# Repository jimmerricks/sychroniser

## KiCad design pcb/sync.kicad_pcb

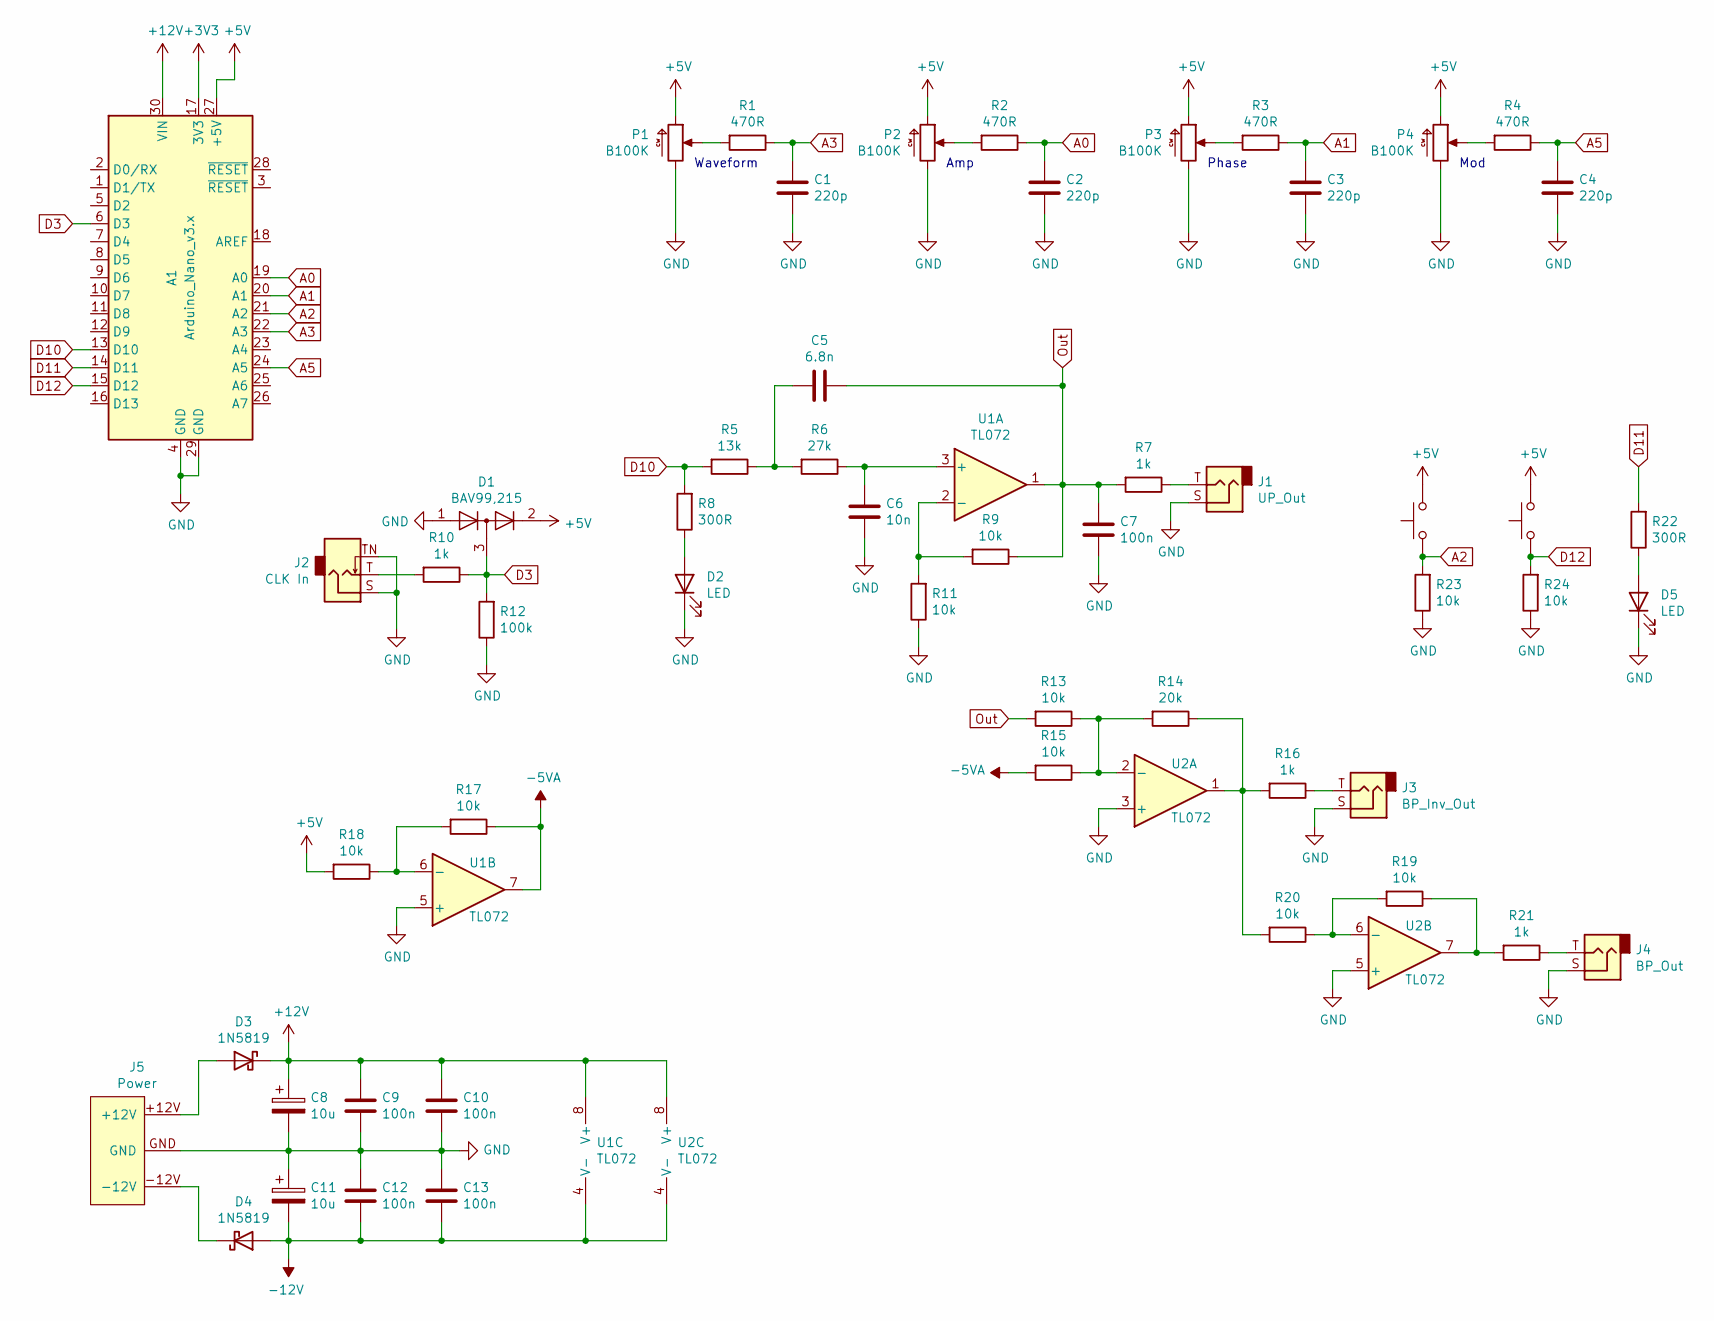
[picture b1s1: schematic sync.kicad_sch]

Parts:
A1: Arduino_Nano_v3.x; Arduino_Nano
C1, C2, C3, C4: 220p; C_0402_1005Metric; LCSC C1530
C5: 6.8n; C_0402_1005Metric; LCSC C1542
C6: 10n; C_0402_1005Metric; LCSC C15195
C7, C9, C10, C12, C13: 100n; C_0402_1005Metric; LCSC C1525
C8, C11: 10u; CP_EIA-3216-18_Kemet-A; LCSC C7171
D1: BAV99,215; SOT-23; LCSC C2500
D2, D5: LED; LED_D3.0mm
D3, D4: 1N5819; D_SOD-323; LCSC C191023
J1: UP_Out; Jack_3.5mm_QingPu_WQP-PJ301M-12
J2: CLK In; Jack_3.5mm_QingPu_WQP-PJ301M-12
J3: BP_Inv_Out; Jack_3.5mm_QingPu_WQP-PJ301M-12
J4: BP_Out; Jack_3.5mm_QingPu_WQP-PJ301M-12
J5: Power; Power_2x5_Vertical
P1, P3, P4: B100K; Potentiometer_AlpsAlpine_RK09L1140_wo_Fix
P2: B100K; Potentiometer_AlpsAlpine_RK09L1140
R1, R2, R3, R4: 470R; R_0402_1005Metric; LCSC C25117
R5: 13k; R_0603_1608Metric; LCSC C22797
R6: 27k; R_0402_1005Metric; LCSC C25771
R7, R10, R16, R21: 1k; R_0402_1005Metric; LCSC C11702
R8, R22: 300R; R_0402_1005Metric; LCSC C25102
R9, R11, R13, R15, R17, R18, R19, R20, R23, R24: 10k; R_0402_1005Metric; LCSC C25744
R12: 100k; R_0402_1005Metric; LCSC C25741
R14: 20k; R_0402_1005Metric; LCSC C25765
SW1, SW2: Button; SW_PUSH_6mm
U1, U2: TL072; SOIC-8_3.9x4.9mm_P1.27mm; LCSC C6961

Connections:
+3V3: A1.17 (3V3)
+5V: A1.27 (+5V), D1.2 (A), P1.CW, P2.CW, P3.CW, P4.CW, R18.2, SW1.2, SW2.2
+12V: A1.30 (VIN), C8.1, C9.2, C10.2, D3.1 (K), U1.8 (V+), U2.8 (V+)
-5VA: R15.2, R17.1, U1.7
-12V: C11.2, C12.1, C13.1, D4.2 (A), U1.4 (V-), U2.4 (V-)
A0: A1.19 (A0), C2.1, R2.1
A1: A1.20 (A1), C3.1, R3.1
A2: A1.21 (A2), R23.2, SW1.1
A3: A1.22 (A3), C1.1, R1.1
A5: A1.24 (A5), C4.1, R4.1
D3: A1.6 (D3), D1.3 (K), R10.1, R12.2
D10: A1.13 (D10), R5.2, R8.2
D11: A1.14 (D11), R22.2
D12: A1.15 (D12), R24.2, SW2.1
GND: A1.4 (GND), A1.29 (GND), C1.2, C2.2, C3.2, C4.2, C6.1, C7.1, C8.2, C9.1, C10.1, C11.1, C12.2, C13.2, D1.1 (K), D2.1 (K), D5.1 (K), J1.S, J2.S, J2.TN, J3.S, J3.TN, J4.S, J5.GND, P1.CCW, P2.CCW, P3.CCW, P4.CCW, R11.1, R12.1, R23.1, R24.1, U1.5 (+), U2.3 (+), U2.5 (+)
unnamed: C5.2, R5.1, R6.2
unnamed: D2.2 (A), R8.1
unnamed: D3.2 (A), J5.+12V
unnamed: D4.1 (K), J5.-12V
unnamed: D5.2 (A), R22.1
unnamed: J1.T, R7.1
unnamed: J2.T, R10.2
unnamed: J3.T, R16.1
unnamed: J4.T, R21.1
unnamed: P1.W, R1.2
unnamed: P2.W, R2.2
unnamed: P3.W, R3.2
unnamed: P4.W, R4.2
unnamed: R14.1, R16.2, R20.2, U2.1
unnamed: R19.1, R21.2, U2.7
unnamed: C6.2, R6.1, U1.3 (+)
unnamed: R9.2, R11.2, U1.2 (-)
unnamed: R17.2, R18.1, U1.6 (-)
unnamed: R13.1, R14.2, R15.1, U2.2 (-)
unnamed: R19.2, R20.1, U2.6 (-)
Out: C5.1, C7.2, R7.2, R9.1, R13.2, U1.1

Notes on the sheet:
Amp
Waveform
Phase
Mod

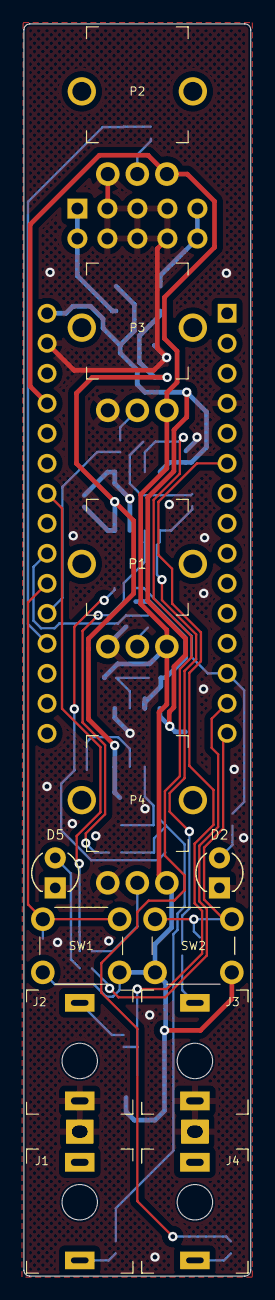
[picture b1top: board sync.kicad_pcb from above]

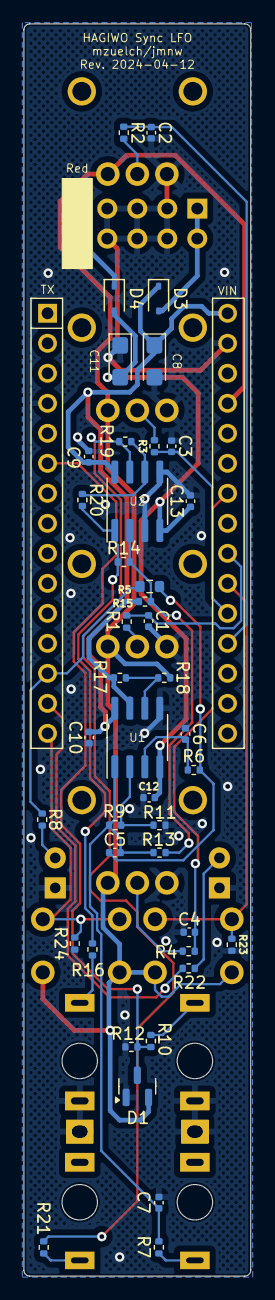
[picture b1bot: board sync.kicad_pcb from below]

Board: 2 copper layers, 19.2 x 106.0 mm, 56 parts (44 on the bottom side), 35 nets.

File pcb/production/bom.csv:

Designator,Footprint,Quantity,Value,LCSC Part #
A1,Arduino_Nano,1,Arduino_Nano_v3.x,
"C1, C2, C3, C4",0402,4,220p,C1530
"C10, C12, C13, C7, C9",0402,5,100n,C1525
"C11, C8",CP_EIA-3216-18_Kemet-A,2,10u,C7171
C5,0402,1,6.8n,C1542
C6,0402,1,10n,C15195
D1,SOT-23,1,"BAV99,215",C2500
"D2, D5",LED_D3.0mm,2,LED,
"D3, D4",D_SOD-323,2,1N5819,C191023
J1,Jack_3.5mm_QingPu_WQP-PJ301M-12,1,UP_Out,
J2,Jack_3.5mm_QingPu_WQP-PJ301M-12,1,CLK In,
J3,Jack_3.5mm_QingPu_WQP-PJ301M-12,1,BP_Inv_Out,
J4,Jack_3.5mm_QingPu_WQP-PJ301M-12,1,BP_Out,
J5,Power_2x5_Vertical,1,Power,
"P1, P3, P4",Potentiometer_AlpsAlpine_RK09L1140_wo_Fix,3,B100K,
P2,Potentiometer_AlpsAlpine_RK09L1140,1,B100K,
"R1, R2, R3, R4",0402,4,470R,C25117
"R10, R16, R21, R7",0402,4,1k,C11702
"R11, R13, R15, R17, R18, R19, R20, R23, R24, R9",0402,10,10k,C25744
R12,0402,1,100k,C25741
R14,0402,1,20k,C25765
"R22, R8",0402,2,300R,C25102
R5,0603,1,13k,C22797
R6,0402,1,27k,C25771
"SW1, SW2",SW_PUSH_6mm,2,Button,
"U1, U2",SOIC-8_3.9x4.9mm_P1.27mm,2,TL072,C6961

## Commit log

2024-07-09 Fixed button circuit, updated pcb for smaller footprints,
